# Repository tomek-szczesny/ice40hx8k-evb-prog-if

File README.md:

# ice40hx8k-evb-prog-if

This is a programming interface for Olimex ICE40HX8K-EVB, that should work with most SBCs on the market (with 40 GPIO pin headers). Tested with Odroid M1.

The board is completely passive and contains only one header and one socket. It may be recreated with a bunch of 2.54mm female-female wires.

It works by writing on-board EEPROM directly through SBC's SPI pins. The EVB's RESET pin is also routed and pulled by the GPIO during programming. The whole process is automated by a makefile crafted for this purpose.

Furthermore, two UART pins on SBC are routed to appropriate pins on FPGA EVB, so with simple UART Verilog modules, one gets a nice debugging interface, all in the same cable. For that, I recommend [uart_tx](https://github.com/tomek-szczesny/ice40_lib/blob/main/uart_tx.v) and [uart_rx](https://github.com/tomek-szczesny/ice40_lib/blob/main/uart_rx.v) Verilog modules from my library. Alternatively, a user may use these two pins as GPIO and put them to some other use.

### The Makefile

A template makefile is included, that can do the following things:

- Build a project, using yosys, nextpnr and so on,

- Burn a project (write onto a EVB connected to a remote SBC)

- Setup the remote SBC to act as a programmer.

This template obvoiusly must be configured to work with your project, by manipulating a bunch of variables at the very beginning of the file.

The "setup" is meant to be run only once. It creates a special user account on remote SBC, that gets rights to use SPI port and one GPIO that operates RESET pin.

### Requirements

In order to use this interface, the remote SBC requires:

- SSH server

- One sudoer (setup only)

- `flashrom`.

### Acknowledgements

All this work is heavily inspired with Andreas Seltenreich's work available [here](https://github.com/anse1/olimex-ice40-notes).

### Disclaimer

Whatever is in this repository is fiction and should not be taken seriously. All similarities with real world designs and coding was not intentional.

##### PCBs

I've got a few to spare, contact me if you're interested.

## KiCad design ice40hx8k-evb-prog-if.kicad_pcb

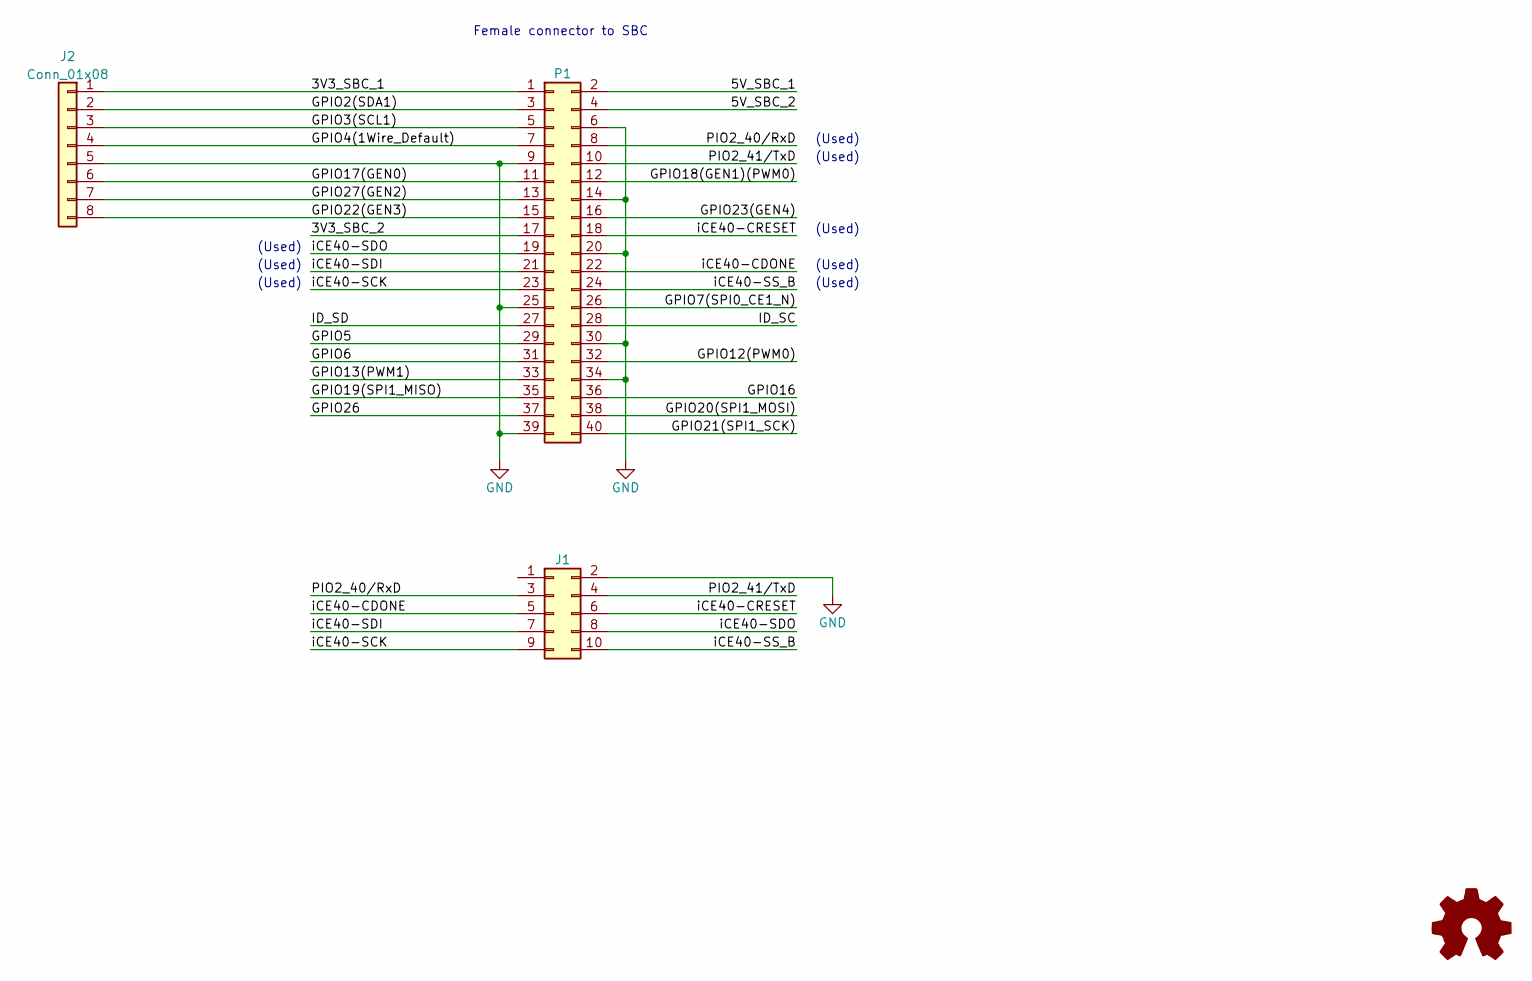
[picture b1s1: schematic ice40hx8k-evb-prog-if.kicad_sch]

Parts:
J1: Conn_02x05_Odd_Even; IDC-Header_2x05_P2.54mm_Vertical
J2: Conn_01x08; PinHeader_1x08_P2.54mm_Vertical
LOGO1: Logo_Open_Hardware_Small; OSHW-Logo_7.5x8mm_SilkScreen
P1: Conn_02x20_Odd_Even; PinSocket_2x20_P2.54mm_Vertical

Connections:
/3V3_SBC_1: J2.1, P1.1
/3V3_SBC_2: P1.17
/5V_SBC_1: P1.2
/5V_SBC_2: P1.4
/GPIO2(SDA1): J2.2, P1.3
/GPIO3(SCL1): J2.3, P1.5
/GPIO4(1Wire_Default): J2.4, P1.7
/GPIO5: P1.29
/GPIO6: P1.31
/GPIO7(SPI0_CE1_N): P1.26
/GPIO12(PWM0): P1.32
/GPIO13(PWM1): P1.33
/GPIO16: P1.36
/GPIO17(GEN0): J2.6, P1.11
/GPIO18(GEN1)(PWM0): P1.12
/GPIO19(SPI1_MISO): P1.35
/GPIO20(SPI1_MOSI): P1.38
/GPIO21(SPI1_SCK): P1.40
/GPIO22(GEN3): J2.8, P1.15
/GPIO23(GEN4): P1.16
/GPIO26: P1.37
/GPIO27(GEN2): J2.7, P1.13
/ID_SC: P1.28
/ID_SD: P1.27
/PIO2_40/RxD: J1.3, P1.8
/PIO2_41/TxD: J1.4, P1.10
/iCE40-CDONE: J1.5, P1.22
/iCE40-CRESET: J1.6, P1.18
/iCE40-SCK: J1.9, P1.23
/iCE40-SDI: J1.7, P1.21
/iCE40-SDO: J1.8, P1.19
/iCE40-SS_B: J1.10, P1.24
GND: J1.2, J2.5, P1.6, P1.9, P1.14, P1.20, P1.25, P1.30, P1.34, P1.39

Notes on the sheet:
(Used)
Female connector to SBC

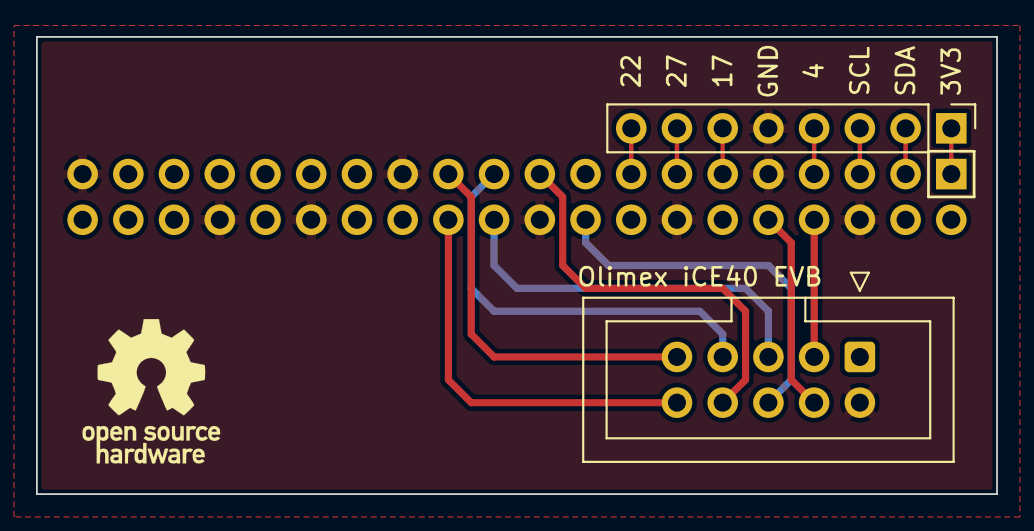
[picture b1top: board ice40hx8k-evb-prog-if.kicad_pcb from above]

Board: 2 copper layers, 53.3 x 25.4 mm, 4 parts (1 on the bottom side), 16 nets.

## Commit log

2022-08-19 Initial commit of KiCAD files
2022-08-19 Moving KiCAD files into a subdir
2022-09-17 Adding template makefile
2022-09-17 Meaningful readme
